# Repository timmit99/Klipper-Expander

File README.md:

# OUTDATED, PLEASE REFER TO THE [VORON HARDWARE REPO](https://github.com/VoronDesign/Voron-Hardware/tree/master/Klipper_Expander) FOR THE LATEST VERSION

# STM32-Klipper-Expander

[Interactive bom](http://htmlpreview.github.io/?https://github.com/VoronDesign/Voron-Hardware/blob/master/Klipper_Expander/KiCad/KlipperExpander_iBOM.html)

Simple MCU board for use with Klipper 3D Printer firmware with:
 - STM32F042F6P6 MCU with internal oscilator
 - SWD header for easy debugging
 - 4 3A Mosfet outputs
 - 2 Thermistor inputs
 - 1 Level Shifted Neopixel output
 - 1 GPIO header
 - I2C Header with Pullup Resistors

 Parts that need to be sourced if assembled by JLC:
  - Micro USB port [Molex 105017-0001](https://www.digikey.com/product-detail/en/molex/1050170001/WM1399CT-ND/2350885) or equivalent [Amazon](https://www.amazon.com/gp/product/B01IQ8VN94)
  - Keystone Fuse Holder [Keystone 3544-2](https://www.digikey.com/product-detail/en/keystone-electronics/3544-2/36-3544-2-ND/316029)
  - Mini Blade Fuse [2A 32V](https://www.digikey.com/product-detail/en/littelfuse-inc/0297002-WXNV/F986-ND/124900), [5A 32V](https://www.digikey.com/product-detail/en/littelfuse-inc/0297005.WXNV/F989-ND/146583), [10A 32V](https://www.digikey.com/product-detail/en/littelfuse-inc/0297010-WXNV/F991-ND/146591), or [Amazon Assortment](https://www.amazon.com/gp/product/B01DYQCXRO/ref=ppx_yo_dt_b_search_asin_title?ie=UTF8&psc=1)
  - 2 Pin Tactile Switch [6 x 3.5mm Button](https://www.digikey.com/product-detail/en/c-k/PTS636-SP43-LFS/CKN12304-ND/10071717) or [Amazon](https://www.amazon.com/flashtree-3x6x4-3H-Momentary-Tactile-Button/dp/B083R566PK/ref=sr_1_13)
  - Screw Terminals [5.08mm Screw Terminals](https://www.digikey.com/product-detail/en/on-shore-technology-inc/OSTTA024163/ED2580-ND/614529)

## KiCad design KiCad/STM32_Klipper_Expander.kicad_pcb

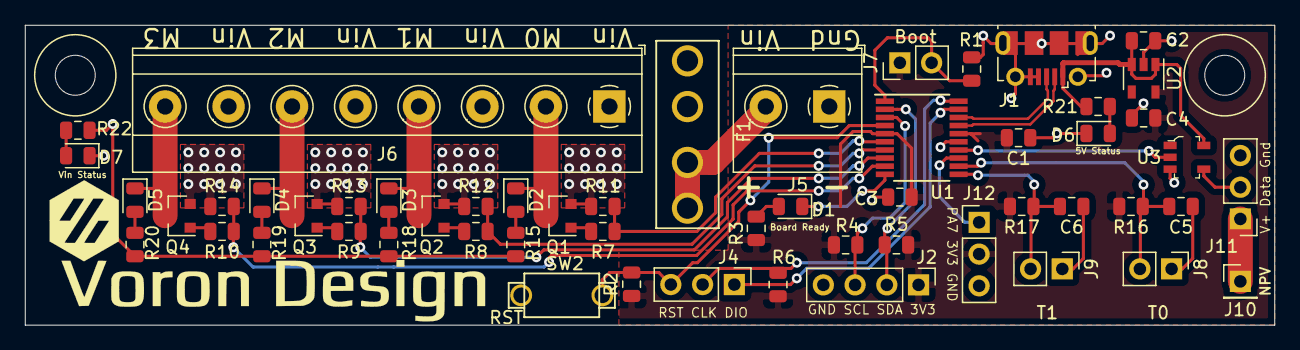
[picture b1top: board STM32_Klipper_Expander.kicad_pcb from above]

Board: 2 copper layers, 100.0 x 24.0 mm, 57 parts (0 on the bottom side), 39 nets.

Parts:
C1, C3: 0.1uF; C_0805_2012Metric
C2, C4, C5, C6: 4.7uF; C_0805_2012Metric
D1, D2, D3, D4, D5, D6, D7: LED; LED_0805_2012Metric
F1: Fuse; 3544-2_FuseHolder
H1, H2: MountingHole; MountingHole_3.2mm_M3
J1: USB_B_Micro; Molex-105017-0001-USBMicroB
J2: Conn_01x04; PinHeader_1x04_P2.54mm_Vertical
J4, J11, J12: Conn_01x03; PinHeader_1x03_P2.54mm_Vertical
J5: Vin; 1x02_ScrewTerminal_Phoenix
J6: Screw_Terminal_01x08; 1x08_ScrewTerminal_Phoenix
J7, J8, J9: Conn_01x02; PinHeader_1x02_P2.54mm_Vertical
J10: Conn_01x01; PinHeader_1x01_P2.54mm_Vertical
Q1, Q2, Q3, Q4: IRLML6344TRPBF; SOT-23
R1, R2, R6, R11, R12, R13, R14: 10K; R_0805_2012Metric
R3, R21: 1K; R_0805_2012Metric
R4, R5, R15, R16, R17, R18, R19, R20, R22: 4.7K; R_0805_2012Metric
R7, R8, R9, R10: 100; R_0805_2012Metric
SW2: SW_SPST; 2PinTactileButton
U1: STM32F042F6Px; TSSOP-20_4.4x6.5mm_P0.65mm
U2: AP2127K-3.3; SOT-23-5
U3: 74LVC1G17; SOT-753

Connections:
+3V3: C1.2, C3.2, C4.2, J2.1, J7.1, J12.2, R2.1, R3.2, R4.2, R5.2, R6.2, R16.2, R17.2, U1.5, U1.16, U2.5
/BOOT0: J7.2, R1.2, U1.1
/D+: J1.3, U1.18
/D-: J1.2, U1.17
/LED: D1.1, U1.10
/Mosfet0: D2.1, J6.2, Q1.3
/Mosfet1: D3.1, J6.4, Q2.3
/Mosfet2: D4.1, J6.6, Q3.3
/Mosfet3: D5.1, J6.8, Q4.3
/SCL: J2.3, R4.1, U1.3
/SDA: J2.2, R5.1, U1.2
/SWDCLK: J4.2, R6.1, U1.20
/SWDIO: J4.1, U1.19
/Vin: F1.1, J6.1, J6.3, J6.5, J6.7, R15.1, R18.1, R19.1, R20.1, R22.2
/~RESET: J4.3, R2.2, SW2.2, U1.4
GND: C1.1, C2.1, C3.1, C4.1, C5.1, C6.1, D6.1, D7.1, J1.4, J1.5, J1.6, J2.4, J5.1, J8.1, J9.1, J11.3, J12.3, Q1.2, Q2.2, Q3.2, Q4.2, R1.1, R11.2, R12.2, R13.2, R14.2, SW2.1, U1.15, U2.2, U3.3
GPIO: J12.1, U1.13
Neopixel: U1.14, U3.2
unnamed: D1.2, R3.1
unnamed: D2.2, R15.2
unnamed: D3.2, R18.2
unnamed: D4.2, R19.2
unnamed: D5.2, R20.2
unnamed: D6.2, R21.1
unnamed: D7.2, R22.1
unnamed: F1.2, J5.2
unnamed: J10.1, J11.1
unnamed: J11.2, U3.4
unnamed: Q1.1, R7.2
unnamed: Q2.1, R8.2
unnamed: Q3.1, R9.2
unnamed: Q4.1, R10.2
PWM0: R7.1, R11.1, U1.6
PWM1: R8.1, R12.1, U1.7
PWM2: R9.1, R13.1, U1.8
PWM3: R10.1, R14.1, U1.9
T0: C5.2, J8.2, R16.1, U1.12
T1: C6.2, J9.2, R17.1, U1.11
VCC: C2.2, J1.1, R21.2, U2.1, U2.3, U3.5

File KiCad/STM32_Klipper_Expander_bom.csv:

Reference, Value, Footprint, Datasheet, LCSC, Alternate PN#, Category, DK_Datasheet_Link, DK_Detail_Page, Description, Digi-Key_PN, Family, MPN, Manufacturer, Status
"C1","0.1uF","Capacitor_SMD:C_0805_2012Metric","~","C49678","","","","","","","","","",""
"C3","0.1uF","Capacitor_SMD:C_0805_2012Metric","~","C49678","","","","","","","","","",""
"U1","STM32F042F6Px","Package_SO:TSSOP-20_4.4x6.5mm_P0.65mm","http://www.st.com/st-web-ui/static/active/en/resource/techni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","C81000","","","","","","","","","",""
"U2","AP2127K-3.3","Package_TO_SOT_SMD:SOT-23-5","https://www.diodes.com/assets/Datasheets/AP2127.pdf","C156285","","","","","","","","","",""
"C4","4.7uF","Capacitor_SMD:C_0805_2012Metric","~","C1779","","","","","","","","","",""
"C2","4.7uF","Capacitor_SMD:C_0805_2012Metric","~","C1779","","","","","","","","","",""
"J1","USB_B_Micro","TRA_KiCad_Footprints:Molex-105017-0001-USBMicroB","~"
"SW2","SW_SPST","TRA_KiCad_Footprints:2PinTactileButton","~"
"R2","10K","Resistor_SMD:R_0805_2012Metric","~","C17414","","","","","","","","","",""
"R6","10K","Resistor_SMD:R_0805_2012Metric","~"
"J4","Conn_01x03","Connector_PinHeader_2.54mm:PinHeader_1x03_P2.54mm_Vertical","~"
"Q1","IRLML6344TRPBF","Package_TO_SOT_SMD:SOT-23","https://www.infineon.com/dgdl/irlml6344pbf.pdf?fileId=5546d4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","C20917","AO3400A","Discrete Semiconductor Products","https://www.infineon.com/dgdl/irlml6344pbf.pdf?fileId=5546d4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","/product-detail/en/infineon-technologies/IRLML6344TRPBF/IRLML6344TRPBFCT-ND/2538168","MOSFET N-CH 30V 5A SOT23","IRLML6344TRPBFCT-ND","Transistors - FETs, MOSFETs - Single","IRLML6344TRPBF","Infineon Technologies","Active"
"R5","4.7K","Resistor_SMD:R_0805_2012Metric","~","C17673","","","","","","","","","",""
"R4","4.7K","Resistor_SMD:R_0805_2012Metric","~","C17673","","","","","","","","","",""
"J2","Conn_01x04","Connector_PinHeader_2.54mm:PinHeader_1x04_P2.54mm_Vertical","~"
"R7","100","Resistor_SMD:R_0805_2012Metric","~","C17408","","","","","","","","","",""
"J5","Vin","TRA_KiCad_Footprints:1x02_ScrewTerminal_Phoenix","~"
"J6","Screw_Terminal_01x08","TRA_KiCad_Footprints:TerminalBlock_Phoenix_MKDS-1,5-8-5.08_1x08_P5.08mm_Horizontal","https://media.digikey.com/pdf/Data%20Sheets/Phoenix%20Contac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"
"J7","Conn_01x02","Connector_PinHeader_2.54mm:PinHeader_1x02_P2.54mm_Vertical","~"
"F1","Fuse","TRA_KiCad_Footprints:3544-2_FuseHolder","~"
"J8","Conn_01x02","Connector_JST:JST_XH_B02B-XH-A_1x02_P2.50mm_Vertical","~"
"C5","10uF","Capacitor_SMD:C_0805_2012Metric","~","C15850","","","","","","","","","",""
"J9","Conn_01x02","Connector_JST:JST_XH_B02B-XH-A_1x02_P2.50mm_Vertical","~"
"C6","10uF","Capacitor_SMD:C_0805_2012Metric","~","C15850","","","","","","","","","",""
"U3","74LVC1G17","Package_TO_SOT_SMD:SOT-353_SC-70-5","http://www.ti.com/lit/sg/scyt129e/scyt129e.pdf","C124293","","","","","","","","","",""
"J10","Conn_01x01","Connector_PinHeader_2.54mm:PinHeader_1x01_P2.54mm_Vertical","~"
"J11","Conn_01x03","Connector_PinHeader_2.54mm:PinHeader_1x03_P2.54mm_Vertical","~"
"J12","Conn_01x02","Connector_PinHeader_2.54mm:PinHeader_1x02_P2.54mm_Vertical","~"
"H1","MountingHole","MountingHole:MountingHole_3.2mm_M3","~"
"H2","MountingHole","MountingHole:MountingHole_3.2mm_M3","~"
"D1","LED","LED_SMD:LED_0805_2012Metric","~","C84256","","","","","","","","","",""
"R3","1K","Resistor_SMD:R_0805_2012Metric","~","C17513","","","","","","","","","",""
"R1","10K","Resistor_SMD:R_0805_2012Metric","~","C17414","","","","","","","","","",""
"R16","10K","Resistor_SMD:R_0805_2012Metric","~","C17414","","","","","","","","","",""
"R17","10K","Resistor_SMD:R_0805_2012Metric","~","C17414","","","","","","","","","",""
"R14","10K","Resistor_SMD:R_0805_2012Metric","~","C17414","","","","","","","","","",""
"R13","10K","Resistor_SMD:R_0805_2012Metric","~","C17414","","","","","","","","","",""
"R12","10K","Resistor_SMD:R_0805_2012Metric","~","C17414","","","","","","","","","",""
"R11","10K","Resistor_SMD:R_0805_2012Metric","~","C17414","","","","","","","","","",""
"R8","100","Resistor_SMD:R_0805_2012Metric","~","C17408","","","","","","","","","",""
"R10","100","Resistor_SMD:R_0805_2012Metric","~","C17408","","","","","","","","","",""
"R9","100","Resistor_SMD:R_0805_2012Metric","~","C17408","","","","","","","","","",""
"Q4","IRLML6344TRPBF","Package_TO_SOT_SMD:SOT-23","https://www.infineon.com/dgdl/irlml6344pbf.pdf?fileId=5546d4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","C20917","AO3400A","Discrete Semiconductor Products","https://www.infineon.com/dgdl/irlml6344pbf.pdf?fileId=5546d4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","/product-detail/en/infineon-technologies/IRLML6344TRPBF/IRLML6344TRPBFCT-ND/2538168","MOSFET N-CH 30V 5A SOT23","IRLML6344TRPBFCT-ND","Transistors - FETs, MOSFETs - Single","IRLML6344TRPBF","Infineon Technologies","Active"
"Q3","IRLML6344TRPBF","Package_TO_SOT_SMD:SOT-23","https://www.infineon.com/dgdl/irlml6344pbf.pdf?fileId=5546d4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","C20917","AO3400A","Discrete Semiconductor Products","https://www.infineon.com/dgdl/irlml6344pbf.pdf?fileId=5546d4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","/product-detail/en/infineon-technologies/IRLML6344TRPBF/IRLML6344TRPBFCT-ND/2538168","MOSFET N-CH 30V 5A SOT23","IRLML6344TRPBFCT-ND","Transistors - FETs, MOSFETs - Single","IRLML6344TRPBF","Infineon Technologies","Active"
"Q2","IRLML6344TRPBF","Package_TO_SOT_SMD:SOT-23","https://www.infineon.com/dgdl/irlml6344pbf.pdf?fileId=5546d4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","C20917","AO3400A","Discrete Semiconductor Products","https://www.infineon.com/dgdl/irlml6344pbf.pdf?fileId=5546d4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","/product-detail/en/infineon-technologies/IRLML6344TRPBF/IRLML6344TRPBFCT-ND/2538168","MOSFET N-CH 30V 5A SOT23","IRLML6344TRPBFCT-ND","Transistors - FETs, MOSFETs - Single","IRLML6344TRPBF","Infineon Technologies","Active"

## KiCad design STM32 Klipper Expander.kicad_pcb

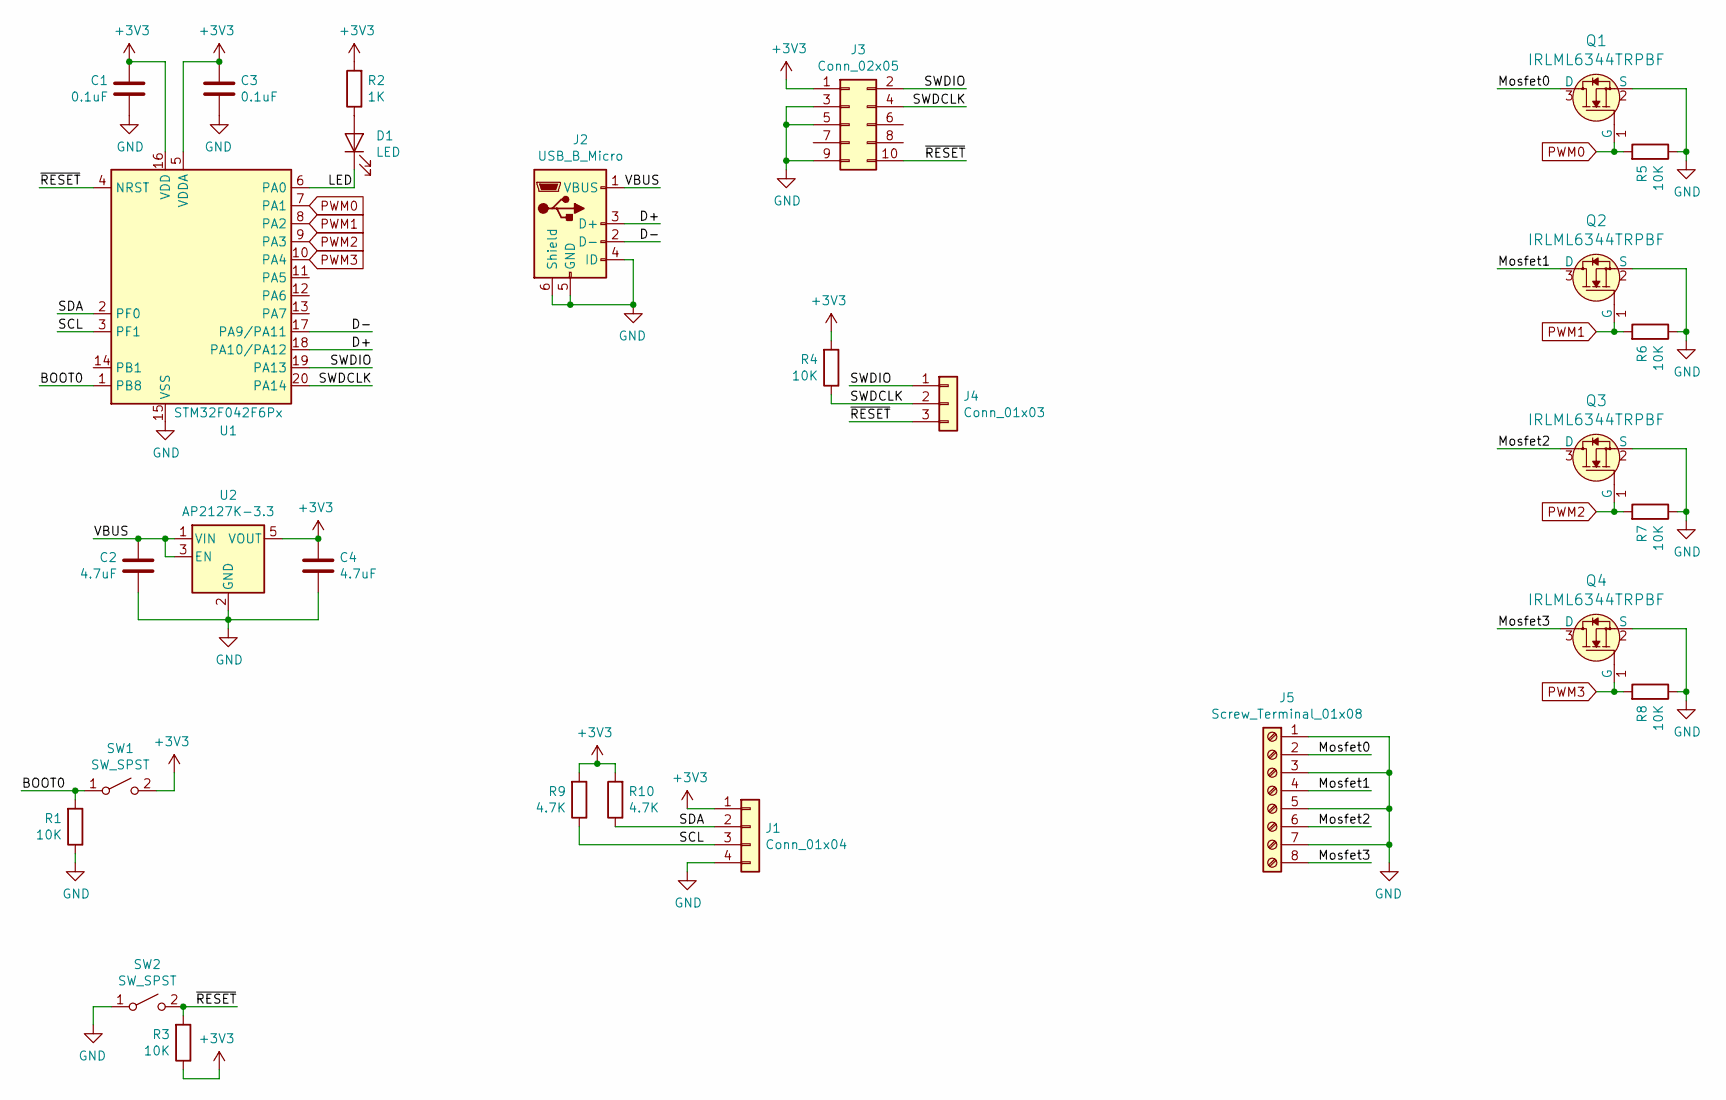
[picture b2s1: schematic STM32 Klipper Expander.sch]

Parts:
C1, C3: 0.1uF; C_0805_2012Metric
C2, C4: 4.7uF; C_0805_2012Metric
D1: LED; LED_0805_2012Metric
J1: Conn_01x04; PinHeader_1x04_P2.54mm_Vertical
J2: USB_B_Micro; USB_Micro-B_Molex_47346-0001
J3: Conn_02x05; PinHeader_2x05_P1.27mm_Vertical
J4: Conn_01x03; PinHeader_1x03_P2.54mm_Vertical
J5: Screw_Terminal_01x08; TerminalBlock_Phoenix_MKDS-1,5-8-5.08_1x08_P5.08mm_Horizont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
Q1, Q2, Q3, Q4: IRLML6344TRPBF; SOT-23-3; MPN IRLML6344TRPBF; Digi-Key_PN IRLML6344TRPBFCT-ND
R1, R3, R4, R5, R6, R7, R8: 10K; R_0805_2012Metric
R2: 1K; R_0805_2012Metric
R9, R10: 4.7K; R_0805_2012Metric
SW1, SW2: SW_SPST; 2PinTactileButton
U1: STM32F042F6Px; TSSOP-20_4.4x6.5mm_P0.65mm
U2: AP2127K-3.3; SOT-23-5

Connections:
+3V3: C1.2, C3.2, C4.2, J1.1, J3.1, R2.2, R3.1, R4.2, R9.2, R10.2, SW1.2 (B), U1.5 (VDDA), U1.16 (VDD), U2.5 (VOUT)
/BOOT0: R1.2, SW1.1 (A), U1.1 (PB8)
/D+: J2.3 (D+), U1.18 (PA10/PA12)
/D-: J2.2 (D-), U1.17 (PA9/PA11)
/LED: D1.1 (K), U1.6 (PA0)
/Mosfet0: J5.2, Q1.3 (D)
/Mosfet1: J5.4, Q2.3 (D)
/Mosfet2: J5.6, Q3.3 (D)
/Mosfet3: J5.8, Q4.3 (D)
/SCL: J1.3, R9.1, U1.3 (PF1)
/SDA: J1.2, R10.1, U1.2 (PF0)
/SWDCLK: J3.4, J4.2, R4.1, U1.20 (PA14)
/SWDIO: J3.2, J4.1, U1.19 (PA13)
/VBUS: C2.2, J2.1 (VBUS), U2.1 (VIN), U2.3 (EN)
/~RESET: J3.10, J4.3, R3.2, SW2.2 (B), U1.4 (NRST)
GND: C1.1, C2.1, C3.1, C4.1, J1.4, J2.4 (ID), J2.5 (GND), J2.6 (Shield), J3.3, J3.5, J3.9, J5.1, J5.3, J5.5, J5.7, Q1.2 (S), Q2.2 (S), Q3.2 (S), Q4.2 (S), R1.1, R5.1, R6.1, R7.1, R8.1, SW2.1 (A), U1.15 (VSS), U2.2 (GND)
unnamed: D1.2 (A), R2.1
PWM0: Q1.1 (G), R5.2, U1.7 (PA1)
PWM1: Q2.1 (G), R6.2, U1.8 (PA2)
PWM2: Q3.1 (G), R7.2, U1.9 (PA3)
PWM3: Q4.1 (G), R8.2, U1.10 (PA4)

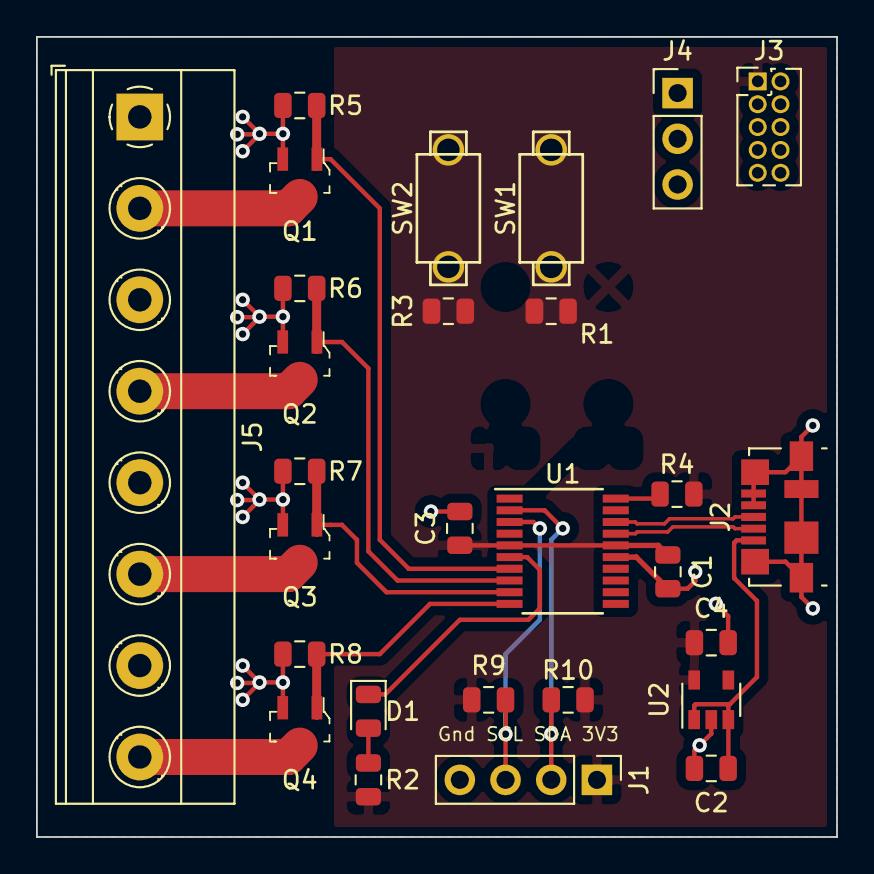
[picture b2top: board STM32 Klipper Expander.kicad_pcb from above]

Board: 2 copper layers, 44.4 x 44.5 mm, 28 parts (0 on the bottom side), 21 nets.

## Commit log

2020-01-15 Organization of Files
2020-01-15 V1 Finilization
    Added all components, silkscreen on bottom with pin names and newer sot-23 mosfets.
2020-01-15 V1 Finalization
    Added all components, silkscreen on bottom with pin names and newer sot-23 mosfets.
2020-01-15 Update to Gerbers
    Updated Gerbers files for production
2020-01-15 Replaced spaces in filename with "_"
    Had issues with some BOM genreation scrips that didnt like filenames/paths with spaces so repalced them with underscores for future use.
    Also added production outputs
2020-01-16 Addition of mounting hole
    APPARENTLY we need some way to mount this....
2020-01-16 Reorganization for more effiecent layout
    Moving to a 100mm x 25mm PCB
2020-01-16 Routing and finalizations
    Completed routing on the thinner variant. Need to gerenate BOM and CPL files for JLCPCB assembly
2020-01-16 Production Files
    Production files created and edited for use with JLCPCB's SMT assembly. The STM32_Klipper_Expander_CPL.csv and STM32_Klipper_Expander_BOM.csv files are used with the online tool to add the part numbe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
2020-01-16 Moving right mounting hole down 1mm
    Moved everything BUT the right M3 Mounting hole down 1mm. Fixed now.
2020-01-16 for real this time
    ACTUALLY pushing the changes and not just some gerber updates...
2020-02-02 Silkscreen changes
2020-02-02 Render updates
    Added update renders of the thin layout board.
2020-02-02 Added Seeed Studio Production files
    Added the Assembly files zip, Gerber zip and BOM in the neede format for SEEED studio. Can always remove the longer lead time parts to hand solder those yourselves.
2020-02-03 file organization
2020-02-03 Duplicate File Removal
2020-02-21 Config and STEP file
    Adding a basic Klipper configuration and .STEP file of the board.
2020-02-22 Addition of Interactive BOM
    Interactive BOM courtesy of https://github.com/openscopeproject/InteractiveHtmlBom/
2020-05-23 Klipper Expander V2
    Update to Klipper Expander that adds status LED's to the 4 mosfet outputs, 5V rail, and Vin rail.
    Also changed 2 capacitors to use the same 4.7uF that are already present lowering the unique part count.
